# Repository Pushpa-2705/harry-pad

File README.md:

# Harry-Pad

### Why did I make it?
As I dont have a keyboard I work on my laptop's keyboard so I can assign specific keys for specific functions i.e. Opening Spotify, Copy paste shortcuts, Screenshot shortcuts etc.

### What was the hardest part about this ?
The hardest part was probably the firmware as I didnt know any coding language so it was pretty challenging

### Bill of Materials
 - 1x Seeed XIAO RP2040
 - 9x SW_Cherry_MX_1.00u_PCB
 - 9x Blank DSA keycaps (Either White or Red)
 - Case (Navy Blue or gray)
 - 1x RE

### Schematic

---

### PCB 

---

### Case
- Bottom

- Top

## Assembly

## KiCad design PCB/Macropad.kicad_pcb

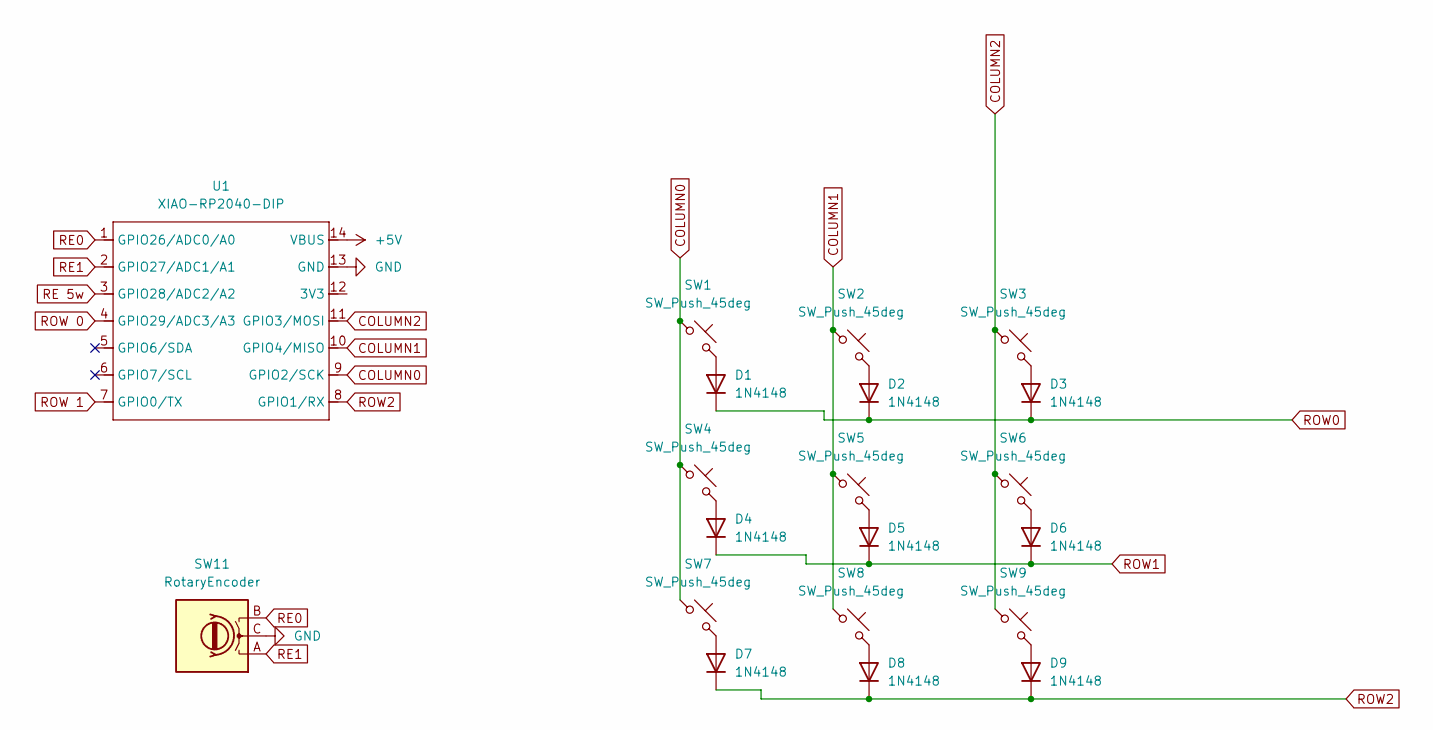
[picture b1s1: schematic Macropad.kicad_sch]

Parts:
D1, D2, D3, D4, D5, D6, D7, D8, D9: 1N4148; D_DO-35_SOD27_P7.62mm_Horizontal
SW1, SW2, SW3, SW4, SW5, SW6, SW7, SW8, SW9: SW_Push_45deg; SW_Cherry_MX_1.00u_PCB
SW11: RotaryEncoder; RotaryEncoder_Alps_EC11E-Switch_Vertical_H20mm_CircularMoun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
U1: XIAO-RP2040-DIP

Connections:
+5V: U1.14 (VBUS)
COLUMN0: SW1.1, SW4.1, SW7.1, U1.9 (GPIO2/SCK)
COLUMN1: SW2.1, SW5.1, SW8.1, U1.10 (GPIO4/MISO)
COLUMN2: SW3.1, SW6.1, SW9.1, U1.11 (GPIO3/MOSI)
GND: SW11.C, U1.13 (GND)
unnamed: D1.2 (A), SW1.2
unnamed: D2.2 (A), SW2.2
unnamed: D3.2 (A), SW3.2
unnamed: D4.2 (A), SW4.2
unnamed: D5.2 (A), SW5.2
unnamed: D6.2 (A), SW6.2
unnamed: D7.2 (A), SW7.2
unnamed: D8.2 (A), SW8.2
unnamed: D9.2 (A), SW9.2
RE0: SW11.B, U1.1 (GPIO26/ADC0/A0)
RE1: SW11.A, U1.2 (GPIO27/ADC1/A1)
RE 5w: U1.3 (GPIO28/ADC2/A2)
ROW0: D1.1 (K), D2.1 (K), D3.1 (K)
ROW1: D4.1 (K), D5.1 (K), D6.1 (K)
ROW2: D7.1 (K), D8.1 (K), D9.1 (K), U1.8 (GPIO1/RX)
ROW 0: U1.4 (GPIO29/ADC3/A3)
ROW 1: U1.7 (GPIO0/TX)

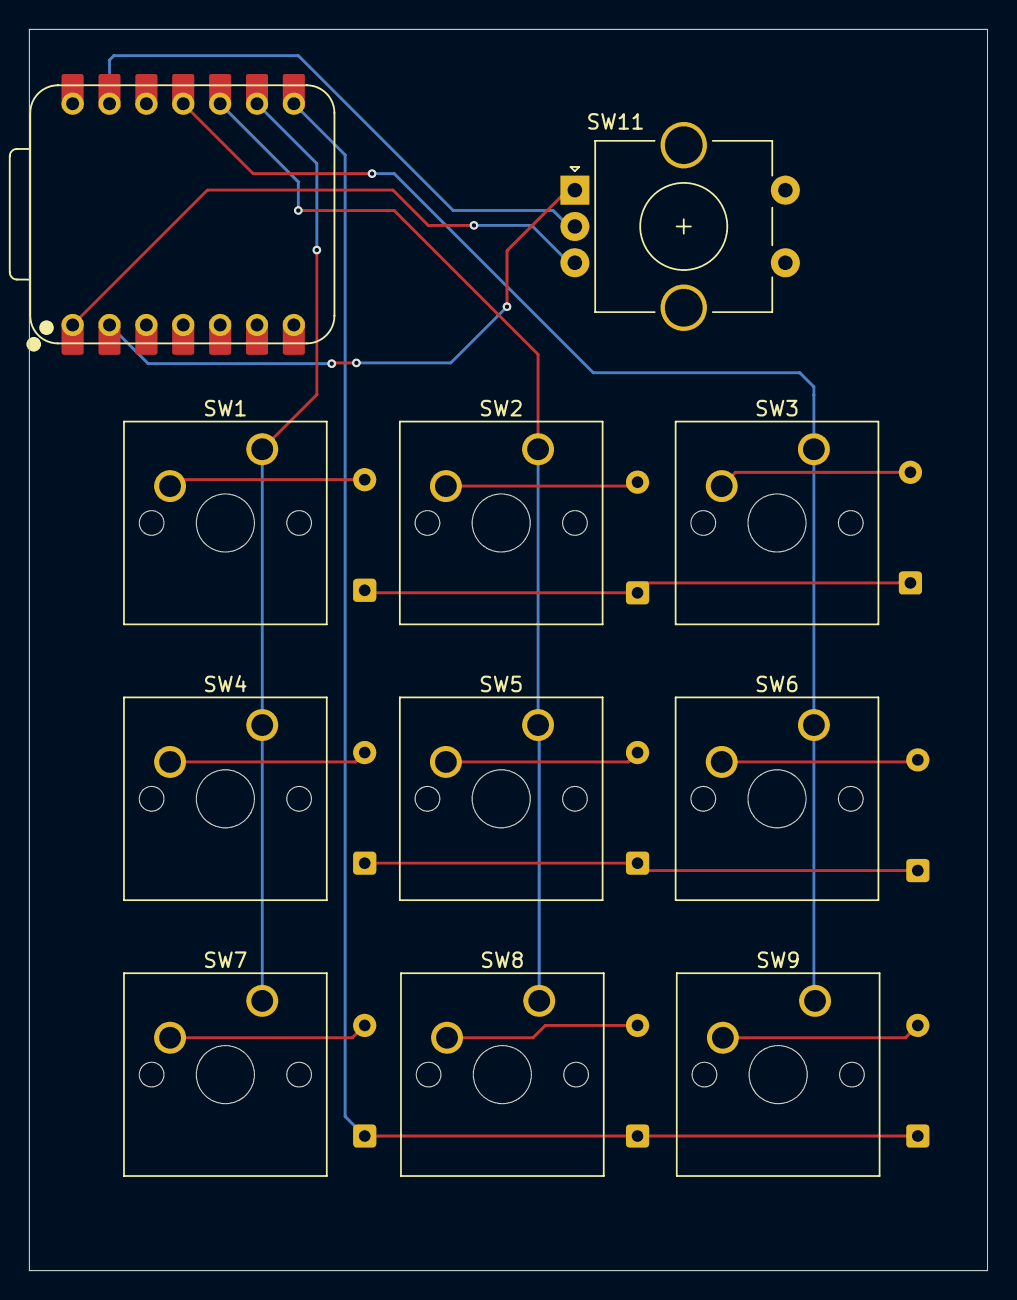
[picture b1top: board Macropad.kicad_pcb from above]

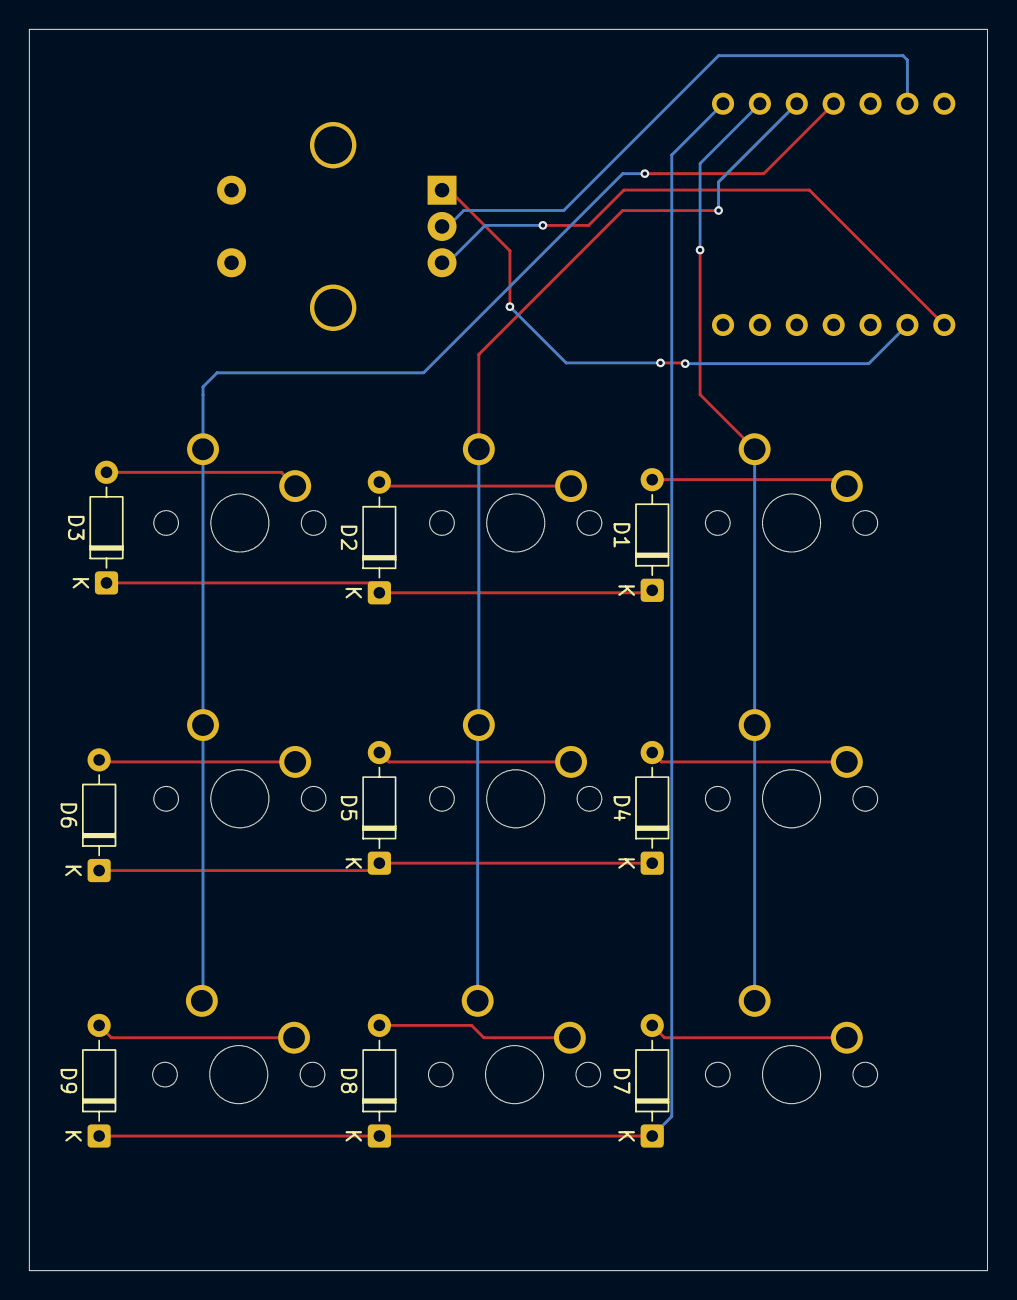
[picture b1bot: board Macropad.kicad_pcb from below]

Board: 2 copper layers, 66.0 x 85.5 mm, 20 parts (9 on the bottom side), 18 nets.
